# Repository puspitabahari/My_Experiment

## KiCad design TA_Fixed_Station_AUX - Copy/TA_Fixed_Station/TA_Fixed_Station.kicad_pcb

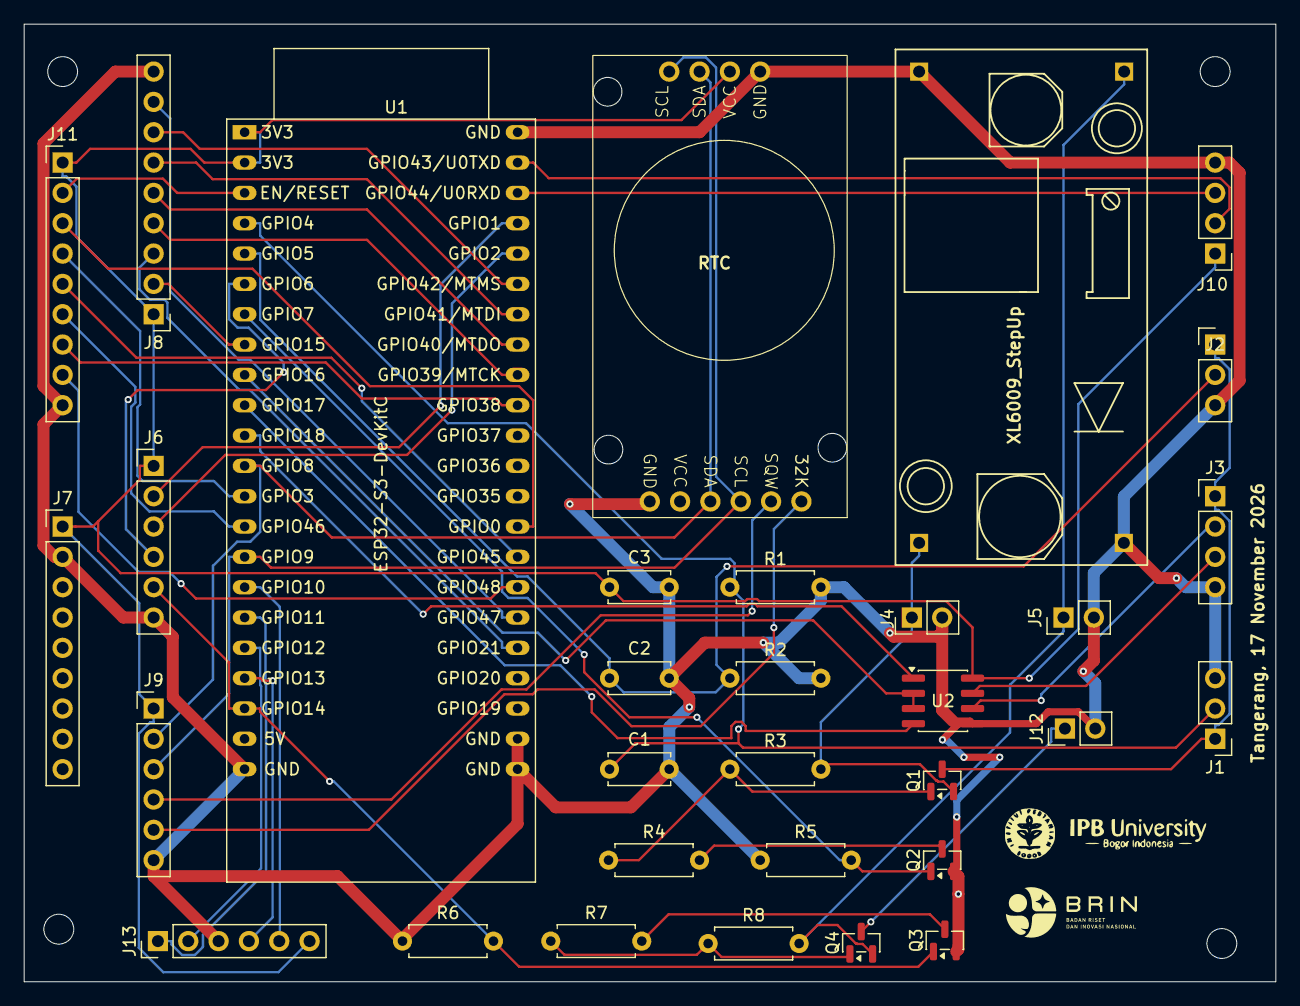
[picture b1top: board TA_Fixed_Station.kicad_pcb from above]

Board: 2 copper layers, 104.8 x 80.2 mm, 38 parts (0 on the bottom side), 46 nets.

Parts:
1, 2, 3, 7: MountingHole_2.5mm
BRIN: LOGO
C1, C2, C3: 100 nF; C_Disc_D5.0mm_W2.5mm_P5.00mm
IPB: LOGO
J1: RIKA RK510-01 4-20 mA #1; PinHeader_1x03_P2.54mm_Vertical
J2: RIKA RK510-01 4-20 mA #2; PinHeader_1x03_P2.54mm_Vertical
J3: RIKA RK510-01 RS485; PinHeader_1x04_P2.54mm_Vertical
J4: Titik Ukur 12 V DC; PinHeader_1x02_P2.54mm_Vertical
J5: Input adaptor 5 V DC; PinHeader_1x02_P2.54mm_Vertical
J6: GPIO_EXPANSION_3V3; PinHeader_1x06_P2.54mm_Vertical
J7: Adafruit_4682_MicroSD_SPI; PinHeader_1x09_P2.54mm_Vertical
J8: GPIO_EXPANSION_2_3V3; PinHeader_1x09_P2.54mm_Vertical
J9: RTC_AUX_3V3; PinHeader_1x06_P2.54mm_Vertical
J10: UART0_3V3; PinHeader_1x04_P2.54mm_Vertical
J11: SPECIAL_PINS_3V3; PinHeader_1x09_P2.54mm_Vertical
J12: Daya modem 5 V; PinHeader_1x02_P2.54mm_Vertical
J13: W25QXX_SPI; PinHeader_1x06_P2.54mm_Vertical
Q1, Q4: AO3401A; SOT-23
Q2, Q3: AO3400A; SOT-23
R1, R2: 120 Ω; R_Axial_DIN0207_L6.3mm_D2.5mm_P7.62mm_Horizontal
R3, R4, R8: 10k Ω; R_Axial_DIN0207_L6.3mm_D2.5mm_P7.62mm_Horizontal
R5, R6: 100k Ω; R_Axial_DIN0207_L6.3mm_D2.5mm_P7.62mm_Horizontal
R7: 330 Ω; R_Axial_DIN0207_L6.3mm_D2.5mm_P7.62mm_Horizontal
U1: ESP32-S3-DevKitC
U2: MAX3485; SOIC-8_3.9x4.9mm_P1.27mm
U3: RTC_DS3231_Module
U4: XL6009_StepUp; XL6009_module

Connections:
+3.3V: C3.1, J6.1, J7.1, J8.1, J9.1, J10.1, J11.1, J13.6, U1.1 (3V3), U1.2 (3V3), U2.8 (VCC), U3.VCC
/12V_SENSOR: J4.1, Q1.2 (S), R3.2, U4.3 (OUT+)
/12V_SOIL_SW: J1.1, J2.1, J3.1, Q1.3 (D)
/+5V_ADAPTER: J5.1, Q4.2 (S), R8.2, U4.1 (IN+)
/+5V_MODEM_SW: J12.1, Q4.3 (D)
/ESP_RX_FROM_MODEM: J6.3, U1.40 (GPIO2/ADC1_CH1)
/ESP_TX_TO_MODEM: J6.2, U1.41 (GPIO1/ADC1_CH0)
/EXP_GPIO0: J11.3, U1.31 (GPIO0)
/EXP_GPIO3: J11.4, U1.13 (GPIO3/ADC1_CH2)
/EXP_GPIO6: J6.4, U1.6 (GPIO6/ADC1_CH5)
/EXP_GPIO15: J8.2, U1.8 (GPIO15/ADC2_CH4/32K_P)
/EXP_GPIO21: J8.3, U1.27 (GPIO21)
/EXP_GPIO38: J11.7, U1.35 (GPIO38)
/EXP_GPIO39: J8.4, U1.36 (GPIO39/MTCK)
/EXP_GPIO40: J8.5, U1.37 (GPIO40/MTDO)
/EXP_GPIO41: J8.6, U1.38 (GPIO41/MTDI)
/EXP_GPIO42: J8.7, U1.39 (GPIO42/MTMS)
/EXP_GPIO45: J11.5, U1.30 (GPIO45)
/EXP_GPIO46: J11.6, U1.14 (GPIO46)
/EXP_GPIO47: J8.8, U1.28 (GPIO47)
/EXP_GPIO48: J11.8, U1.29 (GPIO48)
/FLASH_CS: J13.5, U1.16 (GPIO10/ADC1_CH9)
/FLASH_MISO: J13.4, U1.19 (GPIO13/ADC2_CH2)
/FLASH_MOSI: J13.1, U1.17 (GPIO11/ADC2_CH0)
/FLASH_SCK: J13.2, U1.18 (GPIO12/ADC2_CH1)
/I2C_SCL: J9.3, U1.15 (GPIO9/ADC1_CH8), U3.SCL
/I2C_SDA: J9.2, U1.12 (GPIO8/ADC1_CH7), U3.SDA
/MCU_EN: J11.2, U1.3 (CHIP_PU)
/MODEM_PWR_EN: J6.5, Q3.1 (G), R6.2, U1.20 (GPIO14/ADC2_CH3)
/RS485_A: J3.2, U2.6 (A)
/RS485_B: J3.3, U2.7 (B)
/RS485_DIR: U1.9 (GPIO16/ADC2_CH5/32K_N), U2.2 (~RE), U2.3 (DE)
/RS485_RX: U1.11 (GPIO18/ADC2_CH7), U2.1 (RO)
/RS485_TX: U1.10 (GPIO17/ADC2_CH6), U2.4 (DI)
/RTC_32K: J9.5, U3.32K
/RTC_SQW: J9.4, U3.SQW
/SOIL_ADC1: C1.1, J1.2, R1.1, U1.4 (GPIO4/ADC1_CH3)
/SOIL_ADC2: C2.1, J2.2, R2.1, U1.5 (GPIO5/ADC1_CH4)
/SOIL_PWR_EN: Q2.1 (G), R5.2, U1.7 (GPIO7/ADC1_CH6)
/UART0_RX: J10.3, U1.42 (GPIO44/U0RXD)
/UART0_TX: J10.2, U1.43 (GPIO43/U0TXD)
GND: C1.2, C2.2, C3.2, J1.3, J2.3, J3.4, J4.2, J5.2, J6.6, J7.2, J8.9, J9.6, J10.4, J11.9, J12.2, J13.3, Q2.2 (S), Q3.2 (S), R1.2, R2.2, R5.1, R6.1, U1.22 (GND), U1.23 (GND), U1.24 (GND), U1.44 (GND), U2.5 (GND), U3.GND, U4.2 (IN-), U4.4 (OUT-)
unnamed: Q1.1 (G), R3.1, R4.1
unnamed: Q2.3 (D), R4.2
unnamed: Q3.3 (D), R7.2
unnamed: Q4.1 (G), R7.1, R8.1

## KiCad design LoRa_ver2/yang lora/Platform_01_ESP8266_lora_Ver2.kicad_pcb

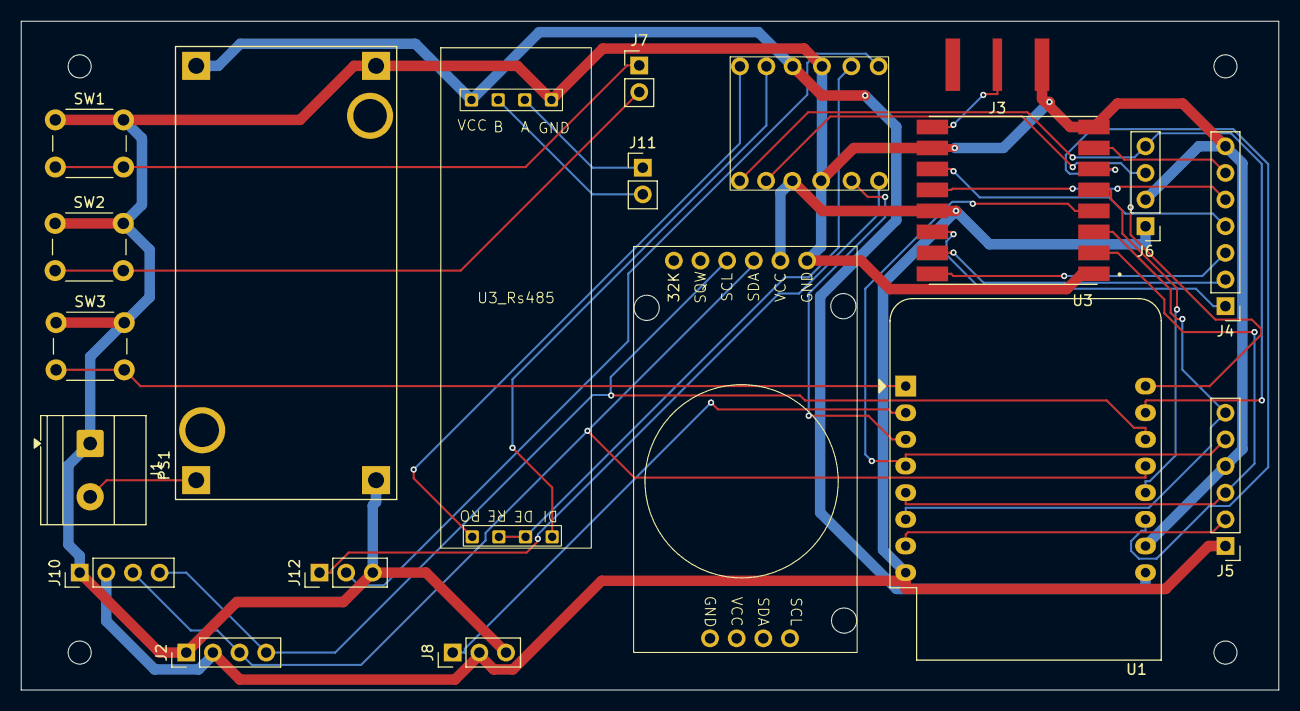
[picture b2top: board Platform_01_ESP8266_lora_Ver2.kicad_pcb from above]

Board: 2 copper layers, 119.9 x 63.8 mm, 24 parts (0 on the bottom side), 33 nets.

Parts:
1: MountingHole_2.2mm_M2_1; MountingHole_2.2mm_M2
2: MountingHole_2.2mm_M2_2; MountingHole_2.2mm_M2
3: MountingHole_2.2mm_M2_3; MountingHole_2.2mm_M2
4: MountingHole_2.2mm_M2
J1: POWER_IN; TerminalBlock_Phoenix_MKDS-1,5-2-5.08_1x02_P5.08mm_Horizont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
J2: I2C_Port; PinHeader_1x04_P2.54mm_Vertical
J3: Conn_Coaxial; 60314202124525
J4: Spare_LoRa; PinHeader_1x07_P2.54mm_Vertical
J5: SPI; PinHeader_1x06_P2.54mm_Vertical
J6: SERIAL_PORT; PinHeader_1x04_P2.54mm_Vertical
J7, J11: Conn_01x02; PinHeader_1x02_P2.54mm_Vertical
J8: ADC_PORT; PinHeader_1x03_P2.54mm_Vertical
J9: RTC; RTC_DS3231_Module
J10: J_PCF8574; PinHeader_1x04_P2.54mm_Vertical
J12: Spare Conn Level Converter; PinHeader_1x03_P2.54mm_Vertical
PS1: LM2596_Module; CONV_MC00100
SW1, SW2, SW3: SW_Push; SW_PUSH_6mm_H5mm
U1: WEMOS_D1_mini; WEMOS_D1_mini_light
U3: RFM95W-915S2; XCVR_RFM95W-915S2
U3_Rs485: RS485_Footprint
U5_Level_RS485: level_converter

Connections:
+3V3: J2.2, J5.1, J6.1, J8.2, J9.3V3 (Pin_3), J10.2, U1.8 (3V3), U3.13 (3.3V), U5_Level_RS485.9 (LV)
+5V: PS1.OUT+, U1.9 (5V), U3_Rs485.VCC, U5_Level_RS485.3 (HV)
/<NO NET>: SW3.2, U1.1 (~RST)
/ADC_A0: J8.1, U1.2 (A0)
/BTN1_CTRL: J7.1, SW1.2
/BTN2_CTRL: J7.2, SW2.2
/DIO0: J4.1, U3.14 (DIO0)
/DIO1: J4.2, U3.15 (DIO1)
/DIO2: J4.3, U3.16 (DIO2)
/DIO3: J4.4, U3.11 (DIO3)
/DIO4: J4.5, U3.12 (DIO4)
/DIO5: J4.6, U3.7 (DIO5)
/I2C_SCL: J2.4, J9.SCL (Pin_2), J10.4, U1.14 (SCL/D1)
/I2C_SDA: J2.3, J9.SDA (Pin_1), J10.3, U1.13 (SDA/D2)
/LORA_NSS: U1.12 (D3), U3.5 (NSS)
/LORA_RST: U1.11 (D4), U3.6 (RESET)
/POWER_IN+: J1.2, PS1.IN+
/RS485_A: J11.1, U3_Rs485.A
/RS485_B: J11.2, U3_Rs485.B
/RS485_DI_5V: U3_Rs485.DI, U5_Level_RS485.2 (HV2)
/RS485_EN: U1.3 (D0), U5_Level_RS485.11 (LV3)
/RS485_EN_5V: U3_Rs485.DE, U3_Rs485.RE, U5_Level_RS485.5 (HV3)
/RS485_RO_5V: U3_Rs485.RO, U5_Level_RS485.1 (HV1)
/SPI_CS: J5.2, U1.7 (CS/D8)
/SPI_MISO: J5.3, U1.5 (MISO/D6), U3.2 (MISO)
/SPI_MOSI: J5.6, U1.6 (MOSI/D7), U3.3 (MOSI)
/SPI_SCK: J5.5, U1.4 (SCK/D5), U3.4 (SCK)
/Spare_HV4: J12.2, U5_Level_RS485.6 (HV4)
/Spare_LV4: J12.1, U5_Level_RS485.12 (LV4)
/UART_RX: J6.4, U1.15 (RX), U5_Level_RS485.7 (LV1)
/UART_TX: J6.3, U1.16 (TX), U5_Level_RS485.8 (LV2)
GND: J1.1, J2.1, J3.2 (Ext), J4.7, J5.4, J6.2, J8.3, J9.GND (Pin_4), J10.1, J12.3, PS1.IN-, PS1.OUT-, SW1.1, SW2.1, SW3.1, U1.10 (GND), U3.1 (GND), U3.8 (GND), U3.10 (GND), U3_Rs485.GND, U5_Level_RS485.4 (GND), U5_Level_RS485.10 (GND)
unnamed: J3.1 (In), U3.9 (ANT)

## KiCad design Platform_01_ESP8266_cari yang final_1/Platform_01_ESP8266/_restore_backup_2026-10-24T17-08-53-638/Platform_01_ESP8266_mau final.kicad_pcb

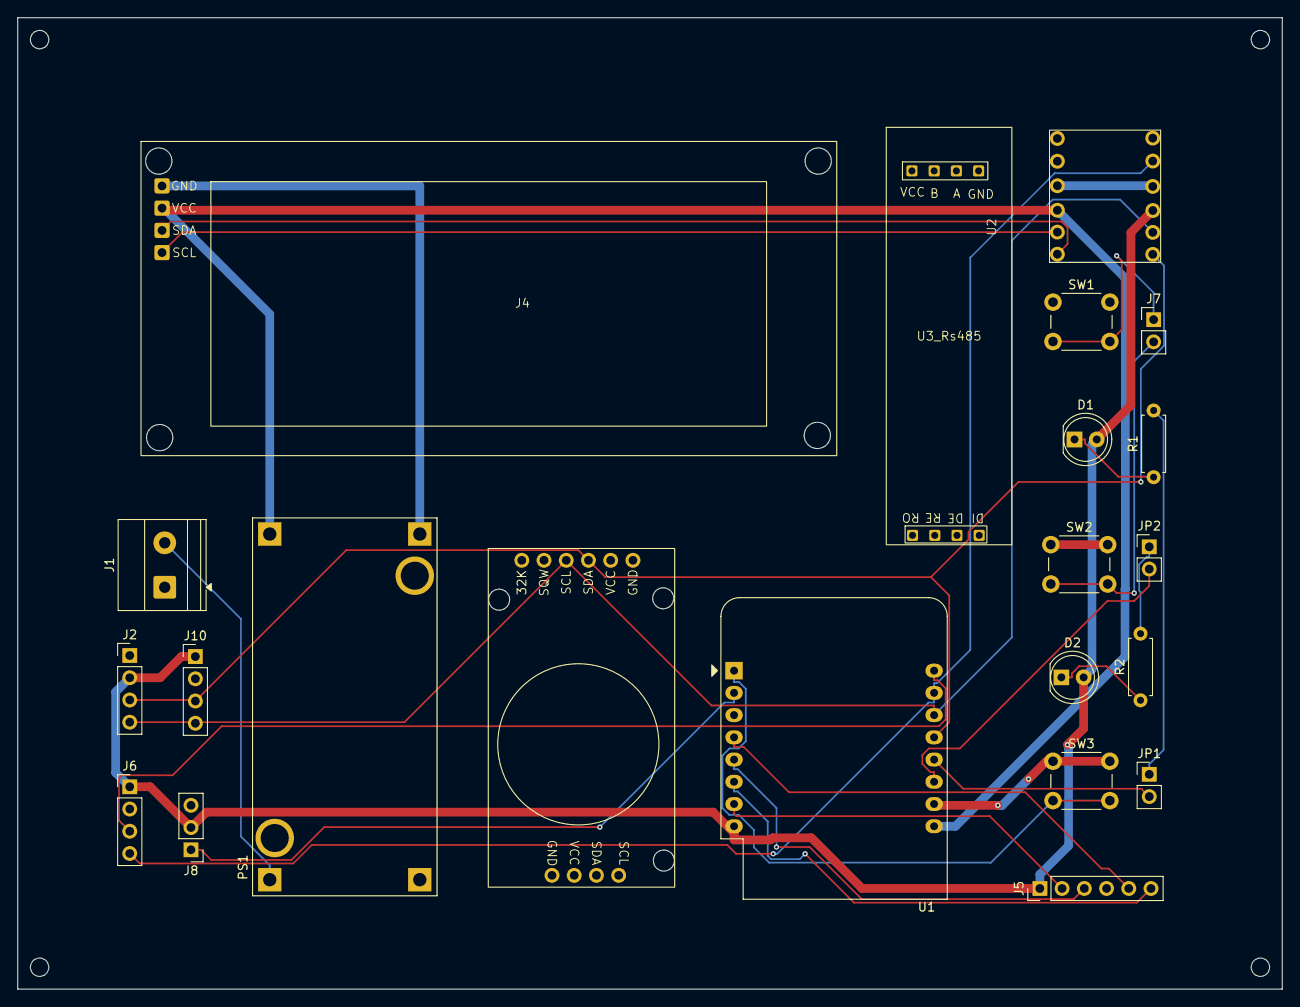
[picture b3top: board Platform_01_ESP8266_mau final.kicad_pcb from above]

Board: 2 copper layers, 144.5 x 111.0 mm, 26 parts (0 on the bottom side), 24 nets.

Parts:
D1, D2: LED; LED_D5.0mm
J1: POWER_IN; TerminalBlock_Phoenix_MKDS-1,5-2-5.08_1x02_P5.08mm_Horizont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
J2: I2C_Port; PinHeader_1x04_P2.54mm_Vertical
J4: LCD; LCDI2C_Module
J5: SPI; PinHeader_1x06_P2.54mm_Vertical
J6: SERIAL_PORT; PinHeader_1x04_P2.54mm_Vertical
J7: Conn_01x02; PinHeader_1x02_P2.54mm_Vertical
J8: ADC_PORT; PinHeader_1x03_P2.54mm_Vertical
J9: RTC; RTC_DS3231_Module
J10: J_PCF8574; PinHeader_1x04_P2.54mm_Vertical
JP1, JP2: SolderJumper_2_Open; PinHeader_1x02_P2.54mm_Vertical
PS1: LM2596_Module; CONV_MC00100
R1, R2: 220; R_Axial_DIN0207_L6.3mm_D2.5mm_P7.62mm_Horizontal
SW1, SW2, SW3: SW_Push; SW_PUSH_6mm_H5mm
U1: WEMOS_D1_mini; WEMOS_D1_mini_light
U2: level_converter
U3_Rs485: RS485_Footprint
a: MountingHole_2.1mm
b: MountingHole_2.1mm
c: MountingHole_2.1mm
d: MountingHole_2.1mm

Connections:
+3V3: D1.2 (A), D2.2 (A), J2.2, J5.1, J6.1, J8.2, J10.1, U1.8 (3V3), U2.9 (LV)
+5V: J4.2, PS1.OUT+, U1.9 (5V), U2.3 (HV)
/<NO NET>: SW3.2, U1.1 (~RST)
/ADC_A0: J8.1, U1.2 (A0)
/BTN1_CTRL: J7.1, SW1.2
/BTN2_CTRL: J7.2, SW2.2
/I2C_SCL: J2.4, J9.SCL (Pin_2), J10.4, U1.14 (SCL/D1), U2.8 (LV2)
/I2C_SDA: J2.3, J9.SDA (Pin_1), J10.3, U1.13 (SDA/D2), U2.7 (LV1)
/LCD_SCL_5V: J4.4, U2.2 (HV2)
/LCD_SDA_5V: J4.3, U2.1 (HV1)
/LED1_CTRL: JP1.2 (B), U1.12 (D3)
/LED2_CTRL: JP2.2 (B), U1.11 (D4)
/POWER_IN+: J1.2, PS1.IN+
/SPI_CS: J5.2, U1.7 (CS/D8)
/SPI_MISO: J5.3, U1.5 (MISO/D6)
/SPI_MOSI: J5.6, U1.6 (MOSI/D7)
/SPI_SCK: J5.5, U1.4 (SCK/D5)
/UART_RX: J6.4, U1.15 (RX), U2.11 (LV3)
/UART_TX: J6.3, U1.16 (TX)
GND: J1.1, J2.1, J4.1, J5.4, J6.2, J8.3, J9.GND (Pin_4), J10.2, PS1.IN-, PS1.OUT-, SW1.1, SW2.1, SW3.1, U1.10 (GND), U2.4 (GND), U2.10 (GND)
unnamed: D1.1 (K), R1.1
unnamed: D2.1 (K), R2.1
unnamed: JP1.1 (A), R1.2
unnamed: JP2.1 (A), R2.2

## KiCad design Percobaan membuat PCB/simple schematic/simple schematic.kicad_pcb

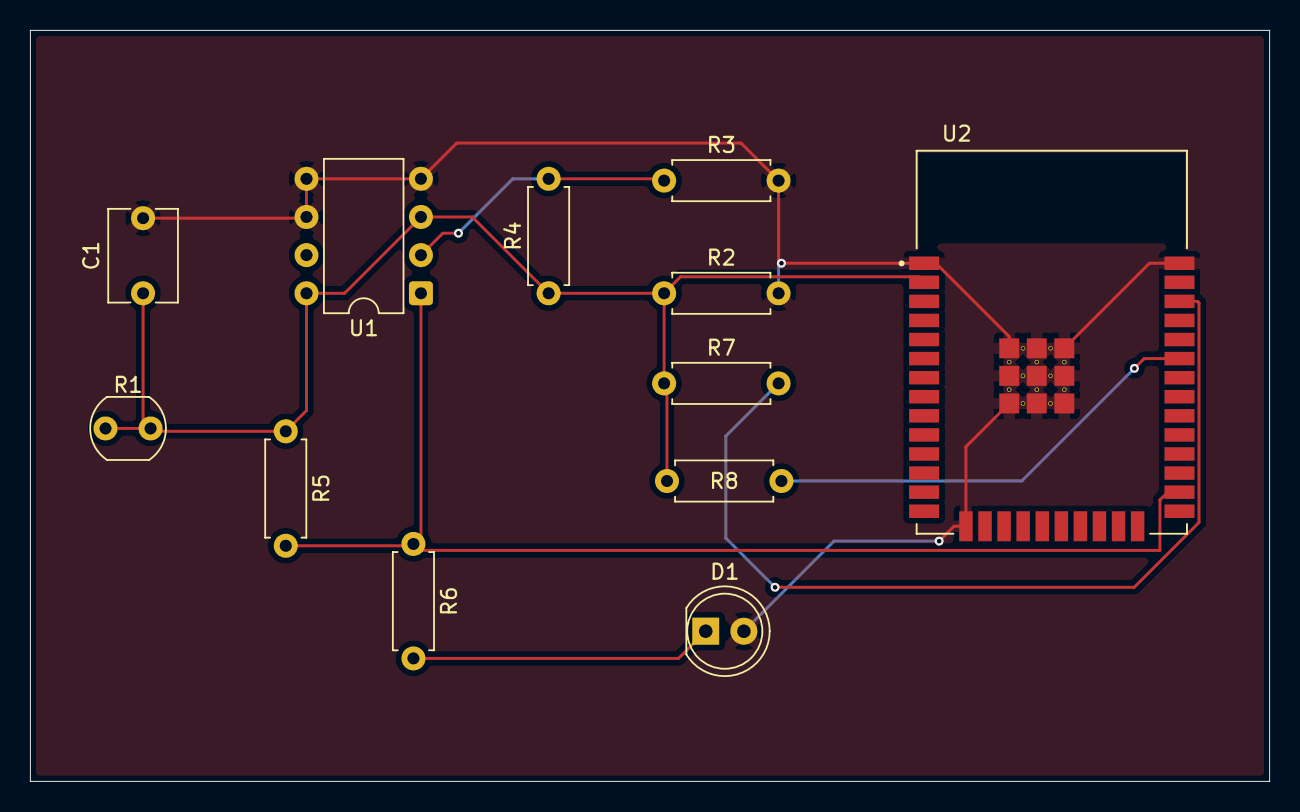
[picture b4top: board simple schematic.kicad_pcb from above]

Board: 2 copper layers, 82.5 x 50.0 mm, 12 parts (0 on the bottom side), 7 nets.

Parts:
C1: 100nF; C_Disc_D6.0mm_W4.4mm_P5.00mm
D1: LED; LED_D5.0mm
R1: GL5528; R_LDR_5.0x4.1mm_P3mm_Vertical
R2, R3, R4, R5: 10K; R_Axial_DIN0207_L6.3mm_D2.5mm_P7.62mm_Horizontal
R6: 330R; R_Axial_DIN0207_L6.3mm_D2.5mm_P7.62mm_Horizontal
R7, R8: 4.7K; R_Axial_DIN0207_L6.3mm_D2.5mm_P7.62mm_Horizontal
U1: LM393; DIP-8_W7.62mm
U2: ESP32-WROOM-32; MODULE_ESP32-WROOM-32

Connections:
+3V3: C1.1, R1.1, R1.2, R2.1, R4.1, R5.1, R7.1, R8.1, U1.3 (+), U1.8 (V+), U2.2 (3V3)
/SCL: R7.2, U2.36 (IO22)
/SDA: R8.2, U2.33 (IO21)
GND: C1.2, D1.2 (A), R2.2, R3.2, U1.4 (V-), U1.5 (+), U1.6 (-), U2.1 (GND), U2.15 (GND), U2.38 (GND), U2.39_1 (GND), U2.39_2 (GND), U2.39_3 (GND), U2.39_4 (GND), U2.39_5 (GND), U2.39_6 (GND), U2.39_7 (GND), U2.39_8 (GND), U2.39_9 (GND), U2.39_10 (GND), U2.39_11 (GND), U2.39_12 (GND), U2.39_13 (GND), U2.39_14 (GND), U2.39_15 (GND), U2.39_16 (GND), U2.39_17 (GND), U2.39_18 (GND), U2.39_19 (GND), U2.39_20 (GND), U2.39_21 (GND)
unnamed: D1.1 (K), R6.2
unnamed: R3.1, R4.2, U1.2 (-)
unnamed: R5.2, R6.1, U1.1, U2.26 (IO4)

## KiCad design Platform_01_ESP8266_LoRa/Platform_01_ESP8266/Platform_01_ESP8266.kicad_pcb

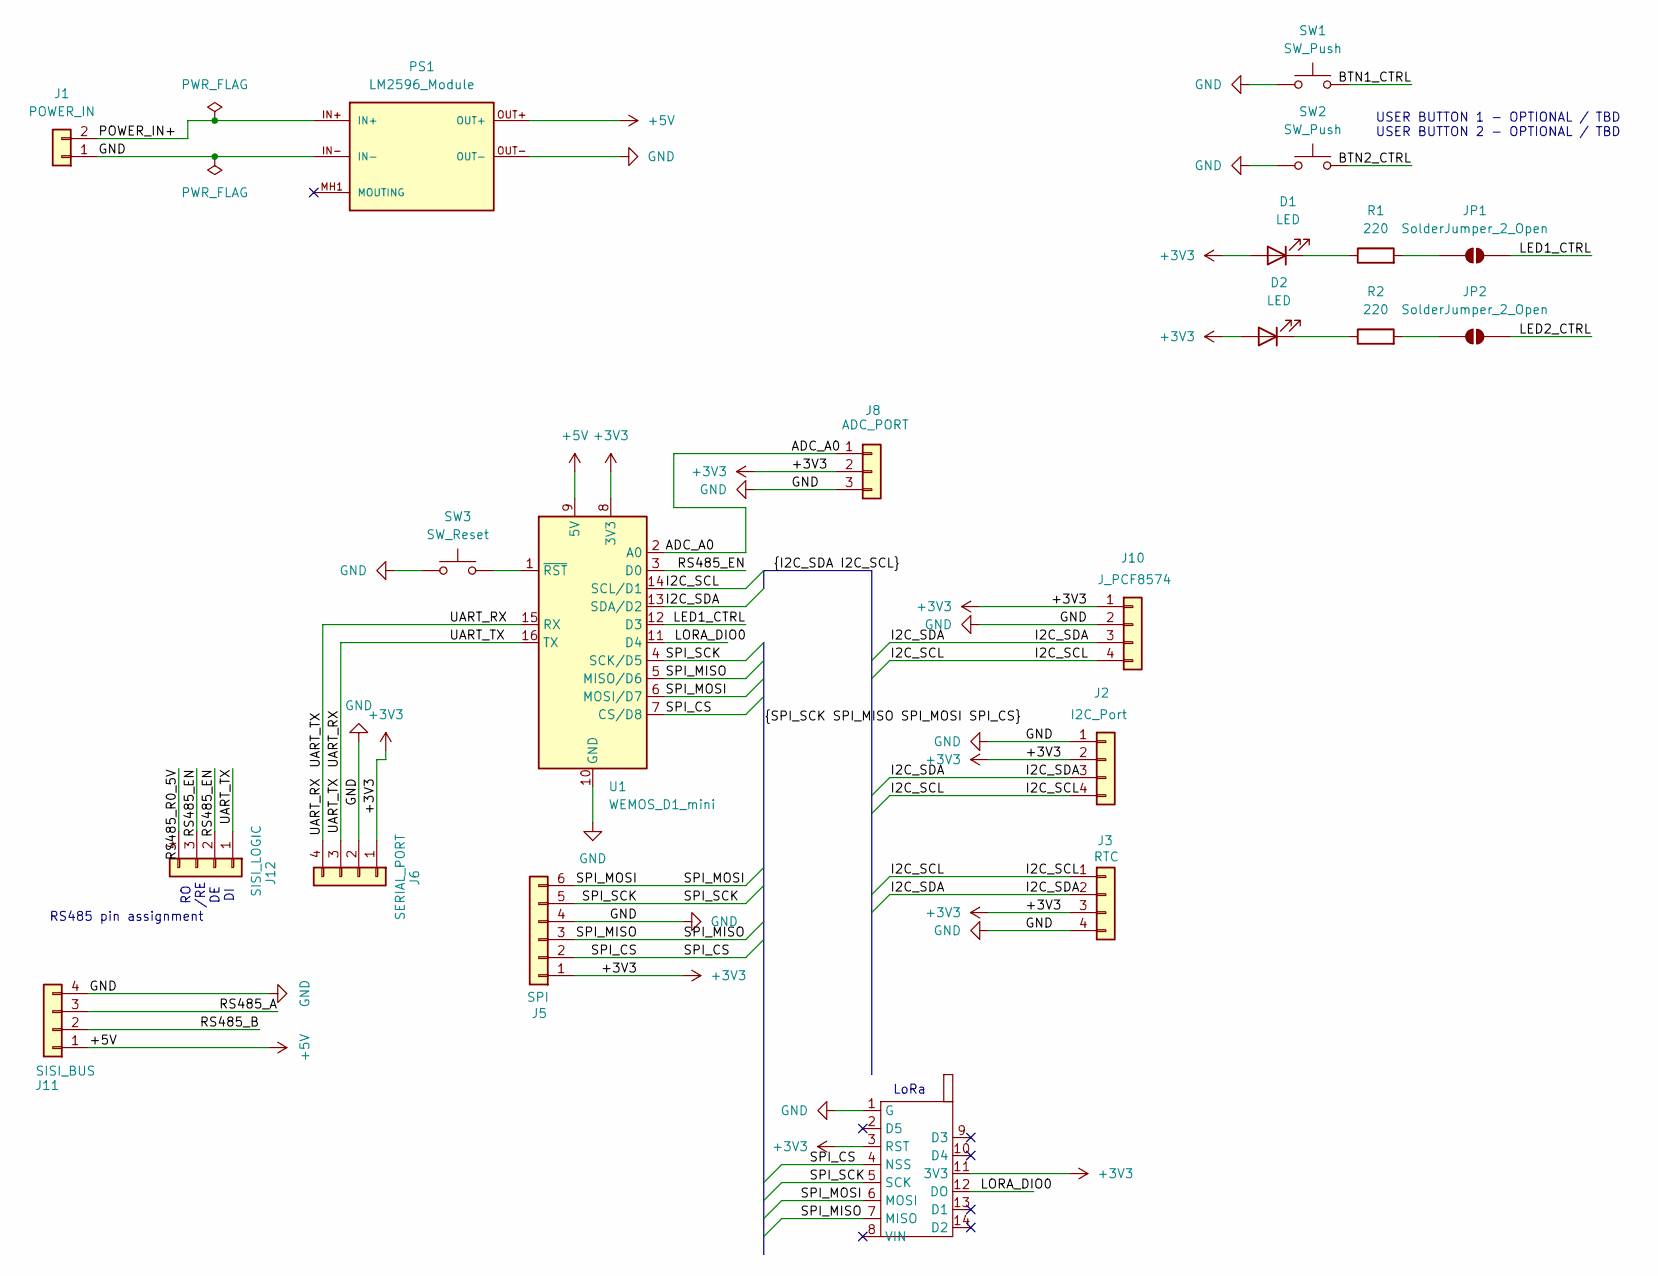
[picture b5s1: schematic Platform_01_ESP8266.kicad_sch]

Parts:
D1, D2: LED; LED_D5.0mm
J1: POWER_IN; TerminalBlock_Phoenix_MKDS-1,5-2-5.08_1x02_P5.08mm_Horizont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
J2: I2C_Port; PinHeader_1x04_P2.54mm_Vertical
J3: RTC; RTC_DS3231_Module
J5: SPI; PinHeader_1x06_P2.54mm_Vertical
J6: SERIAL_PORT; PinHeader_1x04_P2.54mm_Vertical
J8: ADC_PORT; PinHeader_1x03_P2.54mm_Vertical
J10: J_PCF8574; PinHeader_1x04_P2.54mm_Vertical
J11: SISI_BUS; TerminalBlock_Phoenix_MKDS-1,5-4-5.08_1x04_P5.08mm_Horizont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
J12: SISI_LOGIC; PinHeader_1x04_P2.54mm_Vertical
JP1, JP2: SolderJumper_2_Open; PinHeader_1x02_P2.54mm_Vertical
PS1: LM2596_Module; CONV_MC00100; PARTREV NA
R1, R2: 220; R_Axial_DIN0207_L6.3mm_D2.5mm_P7.62mm_Horizontal
SW1, SW2: SW_Push; SW_PUSH_6mm_H5mm
SW3: SW_Reset; SW_PUSH_6mm
U1: WEMOS_D1_mini; WEMOS_D1_mini_light
U3: LoRa

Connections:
+3V3: D1.2 (A), D2.2 (A), J2.2, J3.3, J5.1, J6.1, J8.2, J10.1, U1.8 (3V3), U3.3 (RST), U3.11 (3V3)
+5V: J11.1, PS1.OUT+, U1.9 (5V)
/<NO NET>: SW3.2, U1.1 (~RST)
/ADC_A0: J8.1, U1.2 (A0)
/BTN1_CTRL: SW1.2
/BTN2_CTRL: SW2.2
/I2C_SCL: J2.4, J3.1, J10.4, U1.14 (SCL/D1)
/I2C_SDA: J2.3, J3.2, J10.3, U1.13 (SDA/D2)
/LED1_CTRL: JP1.2 (B), U1.12 (D3)
/LED2_CTRL: JP2.2 (B)
/LORA_DIO0: U1.11 (D4), U3.12 (DO)
/POWER_IN+: J1.2, PS1.IN+
/RS485_A: J11.3
/RS485_B: J11.2
/RS485_EN: J12.2, J12.3, U1.3 (D0)
/RS485_R0_5V: J12.4
/SPI_CS: J5.2, U1.7 (CS/D8), U3.4 (NSS)
/SPI_MISO: J5.3, U1.5 (MISO/D6), U3.7 (MISO)
/SPI_MOSI: J5.6, U1.6 (MOSI/D7), U3.6 (MOSI)
/SPI_SCK: J5.5, U1.4 (SCK/D5), U3.5 (SCK)
/UART_RX: J6.3, J6.4, J12.1, U1.15 (RX), U1.16 (TX)
GND: J1.1, J2.1, J3.4, J5.4, J6.2, J8.3, J10.2, J11.4, PS1.IN-, PS1.OUT-, SW1.1, SW2.1, SW3.1, U1.10 (GND), U3.1 (G)
unnamed: D1.1 (K), R1.1
unnamed: D2.1 (K), R2.1
unnamed: JP1.1 (A), R1.2
unnamed: JP2.1 (A), R2.2

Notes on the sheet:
RO /RE DE DI
RS485 pin assignment
LoRa
USER BUTTON 1 - OPTIONAL / TBD USER BUTTON 2 - OPTIONAL / TBD

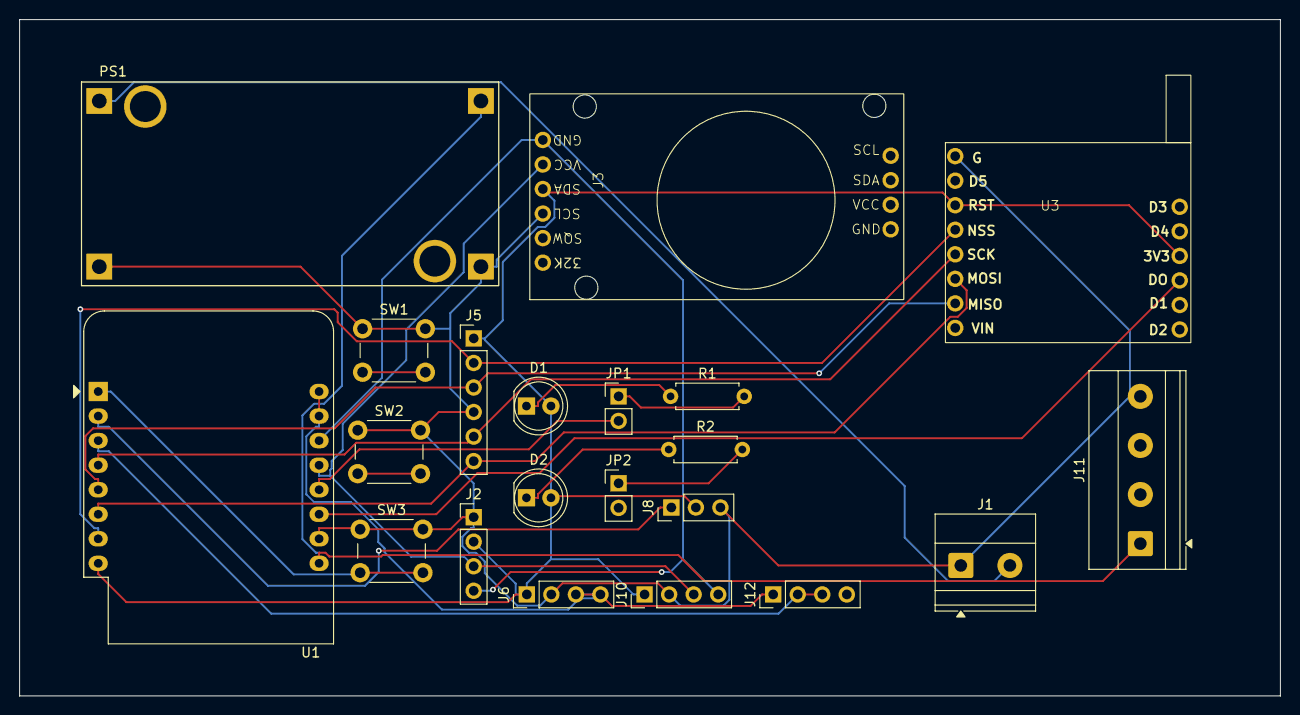
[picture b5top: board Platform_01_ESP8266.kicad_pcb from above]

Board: 2 copper layers, 130.5 x 70.0 mm, 21 parts (0 on the bottom side), 20 nets.
